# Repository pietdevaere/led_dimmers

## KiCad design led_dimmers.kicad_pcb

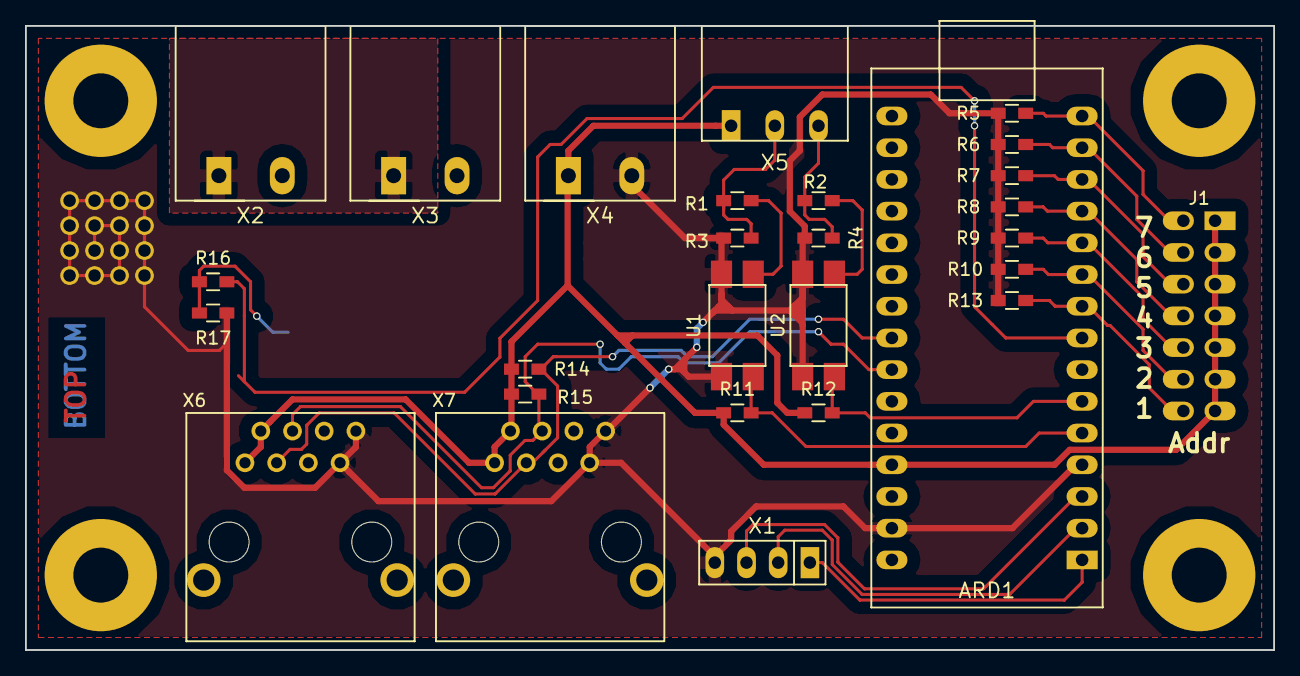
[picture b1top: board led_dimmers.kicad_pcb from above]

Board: 2 copper layers, 100.0 x 50.0 mm, 33 parts (1 on the bottom side), 24 nets.

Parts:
ARD1: ArduinoNano
J1: jumper2x7; Header2x7_254
MOUNT1, MOUNT2, MOUNT3, MOUNT4: MountingHole; HoleM4
Q1: FDB8832; TO-263AB_D2PAK
R1, R2: 1k; R_0603_HandSoldering
R3, R4: 680R; R_0603_HandSoldering
R5, R6, R7, R8, R9, R10, R13, R17: 10K; R_0603_HandSoldering
R11, R12: 10k; R_0603_HandSoldering
R14, R15: 4k7; R_0603_HandSoldering
R16: 100R; R_0603_HandSoldering
U1, U2: PC817; PC817XI
X1: SerialDebug; Header1x4_254
X2, X3, X4: Conn1x2; TerminalBlockPluggable1x2_508
X5: Conn1x3; TerminalBlockPluggable1x3_350
X6, X7: 8P8C; 8P8C-1

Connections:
+5V: ARD1.27, J1.1, J1.2, J1.3, J1.4, J1.5, J1.6, J1.7, R11.1, R12.1, R14.1, R15.1, X4.1, X5.1, X6.1, X6.2, X7.1, X7.2
+12V: X2.1, X3.1
/SCL: ARD1.24, R15.2, X6.4, X7.4
/SDA: ARD1.23, R14.2, X6.3, X7.3
/addr1: ARD1.9, J1.8, R13.1
/addr2: ARD1.10, J1.9, R10.1
/addr3: ARD1.11, J1.10, R9.1
/addr4: ARD1.12, J1.11, R8.1
/addr5: ARD1.13, J1.12, R7.1
/addr6: ARD1.14, J1.13, R6.1
/addr7: ARD1.15, J1.14, R5.1
/led_negative: Q1.4, X3.2
/pwm_ctrl: ARD1.8, R16.2
/reset: ARD1.3, X1.3
/rx: ARD1.2, X1.2
/tx: ARD1.1, X1.1
/usr1: R1.2, R3.2, X5.2
/usr1_safe: ARD1.5, R11.2, U1.4
/usr2: R2.2, R4.2, X5.3
/usr2_safe: ARD1.6, R12.2, U2.4
GND: ARD1.4, ARD1.29, Q1.3, R1.1, R2.1, R5.2, R6.2, R7.2, R8.2, R9.2, R10.2, R13.2, R17.2, U1.2, U1.3, U2.2, U2.3, X1.4, X2.2, X4.2, X6.7, X6.8, X7.7, X7.8
unnamed: Q1.1, R16.1, R17.1
unnamed: R3.1, U1.1
unnamed: R4.1, U2.1

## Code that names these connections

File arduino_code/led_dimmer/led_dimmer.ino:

#include <Wire.h>

#define LED 5
#define USR1 2
#define USR2 3
#define ADDR1 6
#define ADDR2 7
#define ADDR3 8
#define ADDR4 9
#define ADDR5 10
#define ADDR6 11
#define ADDR7 12

#define DIM_BUTTON USR1
#define OPTION_BUTTON USR2

/* dim button constants */
#define DIM_STEP 1
#define DEBOUNCE_TIME 15
#define TOGGLE_TIME 500
#define DIM_TIME 20
//#define DIM_VALUE_TIME 50
#define DIM_SPEED_FAST 50
#define DIM_SPEED_SLOW 18000
#define MINIMUM_TOGGLE_BRIGHTNESS 10

/* button states*/
#define STATE_INACTIVE 0
#define STATE_DEBOUNCING 1
#define STATE_TOGGLE 2
#define STATE_DIM 3

#define ACTION_NOTHING 0
#define ACTION_TOGGLE 4
#define ACTION_DIM 5
#define ACTION_OPTION 6

#define DIRECTION_UP 1
#define DIRECTION_DOWN 2

/* I2C stuff */
#define I2C_ADDR 42
#define I2C_GENERAL_CALL 0
#define I2C_IDDLE 0
#define I2C_ALL_OFF 1

char i2c_last_received = I2C_IDDLE;


/* board IDs
0: all off
1: all off + wake up slave
2: all on
3: all on + wake up slave
4: wake up master
*/

//board id jumper settings
int jumpers[]={ADDR1, ADDR2, ADDR3, ADDR4, ADDR5, ADDR6, ADDR7};
int board_id = 0;

for (int x : jumpers){
    int jumper_value = !digitalRead(x);
    board_id +=1
     if (jumper_value == HIGH){ 
        break;
     }
     
    }

//dimmer speed setting
int dimmer_speed= DIM_SPEED_SLOW;

/* dimmer target setting */
int dimmer_target = 0;
int dimmer_stored_target = 0;
int dim_direction = DIRECTION_UP;

/* dimmer value setting */
int dimmer_value = 0;
long dimmer_value_millis = 0;

/* reading out the dimmer button */
int dim_button_state = STATE_INACTIVE;
long dim_button_millis = 0;


/* reading out the option button */
int option_button_state = STATE_INACTIVE;
long option_button_millis = 0;

/* Called repetedly when dim button is pressed,
 * sets the target brightness value for the led */
int dimmer_step_target(){
    
    dimmer_speed = DIM_SPEED_SLOW;

	if (dim_direction == DIRECTION_UP){
//		dimmer_target += DIM_STEP;
        dimmer_target = dimmer_value + DIM_STEP; //ensure to avoid jumps in led brightness if dimming started during wake-up cycle
	}
	else if (dim_direction == DIRECTION_DOWN){
		dimmer_target -= DIM_STEP;
	}

	if (dimmer_target <= 0){
		dimmer_target = 0;
		dim_direction = DIRECTION_UP;
	}

	if (dimmer_target >= 255){
		dimmer_target = 255;
		dim_direction = DIRECTION_DOWN;
	}

	dimmer_stored_target = dimmer_target;
    

	Serial.print("Dimmer target: ");
	Serial.println(dimmer_target);
}

/* Called once per loop itteration
 * steps the PWM output towards the target
 * value for the led */
int dimmer_step_value(){
	long now_millis = millis();

//	if (now_millis - dimmer_value_millis > DIM_VALUE_TIME &&
    if (now_millis - dimmer_value_millis > dimmer_speed &&
			dimmer_target != dimmer_value) {
		dimmer_value_millis == now_millis;
		if (dimmer_target > dimmer_value) dimmer_value++;
		if (dimmer_target < dimmer_value) dimmer_value--;

		analogWrite(LED, dimmer_value);

		Serial.print("Dimmer value: ");
		Serial.println(dimmer_value);
	}
}

/* Toggle the led */
int toggle_led() {
    
    dimmer_speed = DIM_SPEED_SLOW;
    
	if (dimmer_target > 0) {
		dimmer_target = 0;
	} else {
		dimmer_target = max(dimmer_stored_target, MINIMUM_TOGGLE_BRIGHTNESS);
	}
}

/* Turn led off, and store dim status */
int all_led_off() {
     
    dimmer_speed = DIM_SPEED_FAST;
    dimmer_target = 0;
    
}

int all_led_on() {
     
    dimmer_speed = DIM_SPEED_FAST;
    dimmer_target = 255;
    
}

// set target and speed for wake up light
int wake_set_target() {
    
    dimmer_speed = DIM_SPEED_SLOW;
    dimmer_target = 255;
    
   
    
}


int option_button_task(){
    switch (board_id){
            case(0 OR 1):
            all_led_off();
            Serial.println("LOCAL ALL LED OFF");
            i2c_broadcast(I2C_ALL_OFF);
            
            case(2 OR 3):
            all_led_on();
            Serial.println("LOCAL ALL LED ON");
            i2c_broadcast(I2C_ALL_ON);
            
            case(4):
            wake_set_target();
            Serial.println("LOCAL WAKE SET TARGET");
            i2c_broadcast(I2C_WAKE_SET);
    }
    
}


/* Read and debounce the dim button (light switch)
 * decide which action (Nothing, Dim or Toggle) to
 * take */
int read_dim_button() {
  int button_value = !digitalRead(DIM_BUTTON);
  long millis_now = millis();
  
  if (button_value == LOW) {
    if (dim_button_state == STATE_TOGGLE) {
      dim_button_state = STATE_INACTIVE;
      return ACTION_TOGGLE;
    }
    dim_button_state = STATE_INACTIVE;
    return ACTION_NOTHING;
  }
  
  if (button_value == HIGH) {
    switch(dim_button_state){
      case STATE_INACTIVE:
        dim_button_millis = millis_now;
        dim_button_state = STATE_DEBOUNCING;
        break;
        
      case STATE_DEBOUNCING:
        if (millis_now - dim_button_millis > DEBOUNCE_TIME) {
          dim_button_millis = millis_now;
          dim_button_state = STATE_TOGGLE;
        }
        break;
        
      case STATE_TOGGLE:
        if (millis_now - dim_button_millis > TOGGLE_TIME) {
          dim_button_millis = millis_now;
          dim_button_state = STATE_DIM;
          return ACTION_DIM;
        }
        break;
        
      case STATE_DIM:
          if (millis_now - dim_button_millis > DIM_TIME) {
          dim_button_millis = millis_now;
          dim_button_state = STATE_DIM;
          return ACTION_DIM;
        }
        break;
    }
  }
  return ACTION_NOTHING;
}


int read_option_button() {
  int button_value = !digitalRead(OPTION_BUTTON);
  long millis_now = millis();

  if (button_value == LOW) {
    if (option_button_state == STATE_TOGGLE) {
      option_button_state = STATE_INACTIVE;
      return ACTION_OPTION;
    }
    option_button_state = STATE_INACTIVE;
    return ACTION_NOTHING;
  }

  if (button_value == HIGH) {
    switch(option_button_state){
      case STATE_INACTIVE:
        option_button_millis = millis_now;
        option_button_state = STATE_DEBOUNCING;
        break;

      case STATE_DEBOUNCING:
        if (millis_now - option_button_millis > DEBOUNCE_TIME) {
          option_button_millis = millis_now;
          option_button_state = STATE_TOGGLE;
        }
        break;
    }
  }
  return ACTION_NOTHING;
}

/* I2C Rx handler */
void i2c_rx_handler(int byteCount){
	/* Note that only last received byte will be acted upon */
	digitalWrite(13, !digitalRead(13));
	while (Wire.available()){
		i2c_last_received =  Wire.read();
	}
}

/* nice wrapper to send i2c commands */
void i2c_broadcast(char data){
	Wire.beginTransmission(I2C_ADDR);
	Wire.write(data);
	Wire.endTransmission();
}


// the setup routine runs once when you press reset:
void setup() {                

  pinMode(LED, OUTPUT);

  Wire.begin(I2C_ADDR);
  Wire.onReceive(i2c_rx_handler);

  Serial.begin(115200);
  Serial.println("Good morning. I am the dimmer");
}

// the loop routine runs over and over again forever:
void loop() {
    int dim_button_action;
	int option_button_action;

	/* DIM BUTTON */
    dim_button_action = read_dim_button();
    if (dim_button_action == ACTION_TOGGLE) {
		Serial.println("TOGGLE");
		toggle_led();
	}
    if (dim_button_action == ACTION_DIM) {
		Serial.println("DIM");
		dimmer_step_target();
	}

	/* OPTION BUTTON */
	option_button_action = read_option_button();
	if (option_button_action == ACTION_OPTION){
		Serial.println("OPTION BUTTON TASK");
		option_button_task();
	}

	/* I2C RECEIVE */
    switch (i2c_last_received){
            case(I2C_ALL_OFF):
            Serial.println("I2C ALL OFF");
            all_led_off();
            
            case(I2C_ALL_ON):
            Serial.println("I2C ALL ON");
            all_led_on();
            
            case(I2C_WAKE_SET):
            Serial.println("I2C WAKE SET");
            wake_set_target();
    
    }
    
/*	if (i2c_last_received == I2C_ALL_OFF) {
		Serial.println("I2C ALL OFF");
		all_led_off();
	}
*/
	i2c_last_received = I2C_IDDLE;

	dimmer_step_value();
    
}

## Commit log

2017-12-31 forgot to commit
2017-12-31 added mounting annotation
2017-12-31 added pdf sch
2018-04-01 changes from naas
